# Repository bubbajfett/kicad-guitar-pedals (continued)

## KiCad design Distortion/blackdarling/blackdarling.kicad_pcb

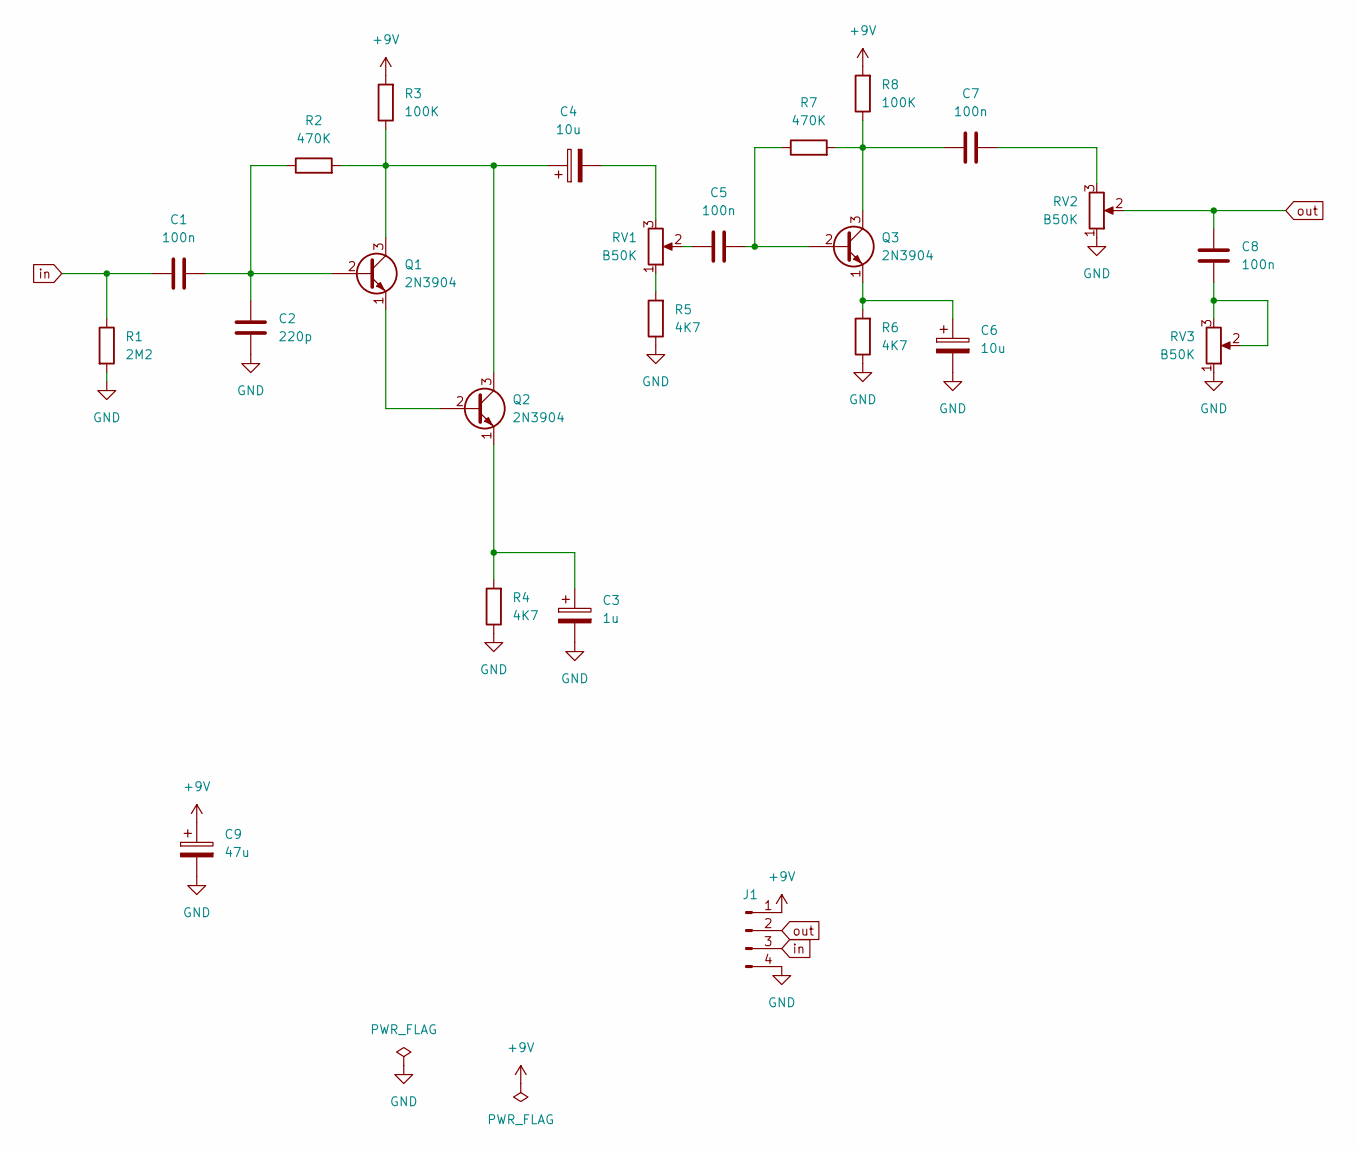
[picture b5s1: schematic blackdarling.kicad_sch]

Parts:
C1, C5, C7, C8: 100n; C_Rect_L7.0mm_W2.5mm_P5.00mm
C2: 220p; C_Disc_D3.8mm_W2.6mm_P2.50mm
C3: 1u; CP_Radial_D5.0mm_P2.00mm
C4, C6: 10u; CP_Radial_D5.0mm_P2.00mm
C9: 47u; CP_Radial_D6.3mm_P2.50mm
J1: Conn_01x04_Pin; PinHeader_1x04_P2.54mm_Vertical
Q1, Q2, Q3: 2N3904; TO-92_Inline
R1: 2M2; R_Axial_DIN0207_L6.3mm_D2.5mm_P10.16mm_Horizontal
R2, R7: 470K; R_Axial_DIN0207_L6.3mm_D2.5mm_P10.16mm_Horizontal
R3, R8: 100K; R_Axial_DIN0207_L6.3mm_D2.5mm_P10.16mm_Horizontal
R4, R5, R6: 4K7; R_Axial_DIN0207_L6.3mm_D2.5mm_P10.16mm_Horizontal
RV1, RV2, RV3: B50K; Pot_Underside

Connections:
+9V: C9.1, J1.1, R3.2, R8.2
GND: C2.1, C3.2, C6.2, C9.2, J1.4, R1.2, R4.1, R5.1, R6.1, RV2.1, RV3.1
unnamed: C4.2, RV1.3
unnamed: C5.1, RV1.2
unnamed: C7.1, RV2.3
unnamed: C8.2, RV3.2, RV3.3
unnamed: C1.2, C2.2, Q1.2 (B), R2.1
unnamed: C4.1, Q1.3 (C), Q2.3 (C), R2.2, R3.1
unnamed: Q1.1 (E), Q2.2 (B)
unnamed: C3.1, Q2.1 (E), R4.2
unnamed: C5.2, Q3.2 (B), R7.1
unnamed: C7.2, Q3.3 (C), R7.2, R8.1
unnamed: C6.1, Q3.1 (E), R6.2
unnamed: R5.2, RV1.1
in: C1.1, J1.3, R1.1
out: C8.1, J1.2, RV2.2

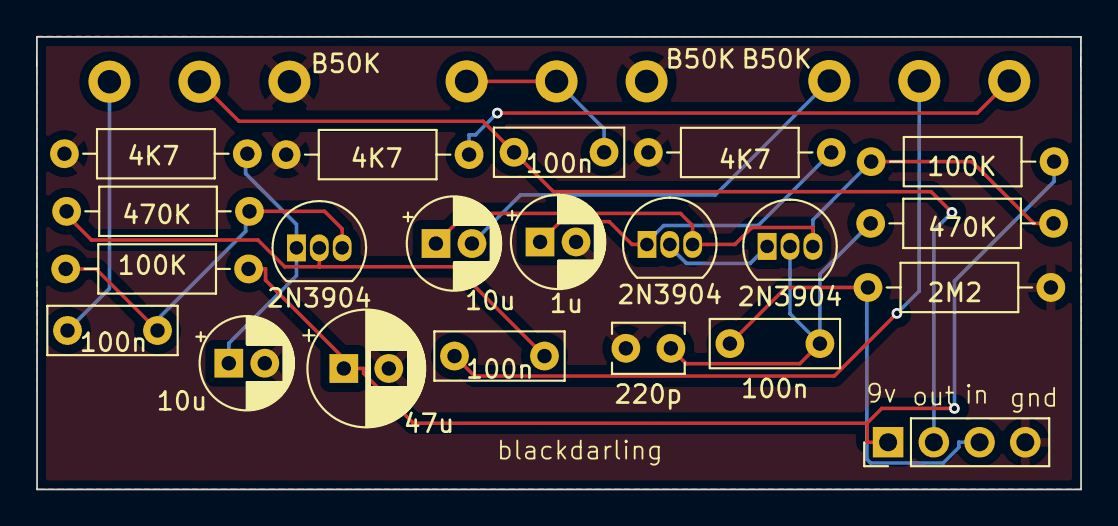
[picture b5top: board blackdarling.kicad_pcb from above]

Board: 2 copper layers, 58.0 x 25.1 mm, 24 parts (0 on the bottom side), 16 nets.

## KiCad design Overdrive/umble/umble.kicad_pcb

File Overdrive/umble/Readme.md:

# Umble

This is from Runoffgrove Umble, and is based on that schematic.

This pedal is verified.  It is very loud.  You must adjust the biases
to around 4.5v on pin3 of each trimmer.

Out of an enclosure it has a lot of noise, which I think is common for
higher-gain pedals.   All 5 controls seem to work the way that they are
intended.

This only has footprints for SMD because I did not think there was enough
room for a through-hole and SMD.    I soldered on the J201 first, and then
used other pads on the empty pcb to test that the soldered J201s were
functional.  All 4 tested out as NJFET with a peak tester.

Sourcing all the pots with a RG097 footprint was a bit of a PITA, but
I do love how tight these are when it is all boxed up.

Not boxed yet, tho.

All trademarks belong to their respective owners.

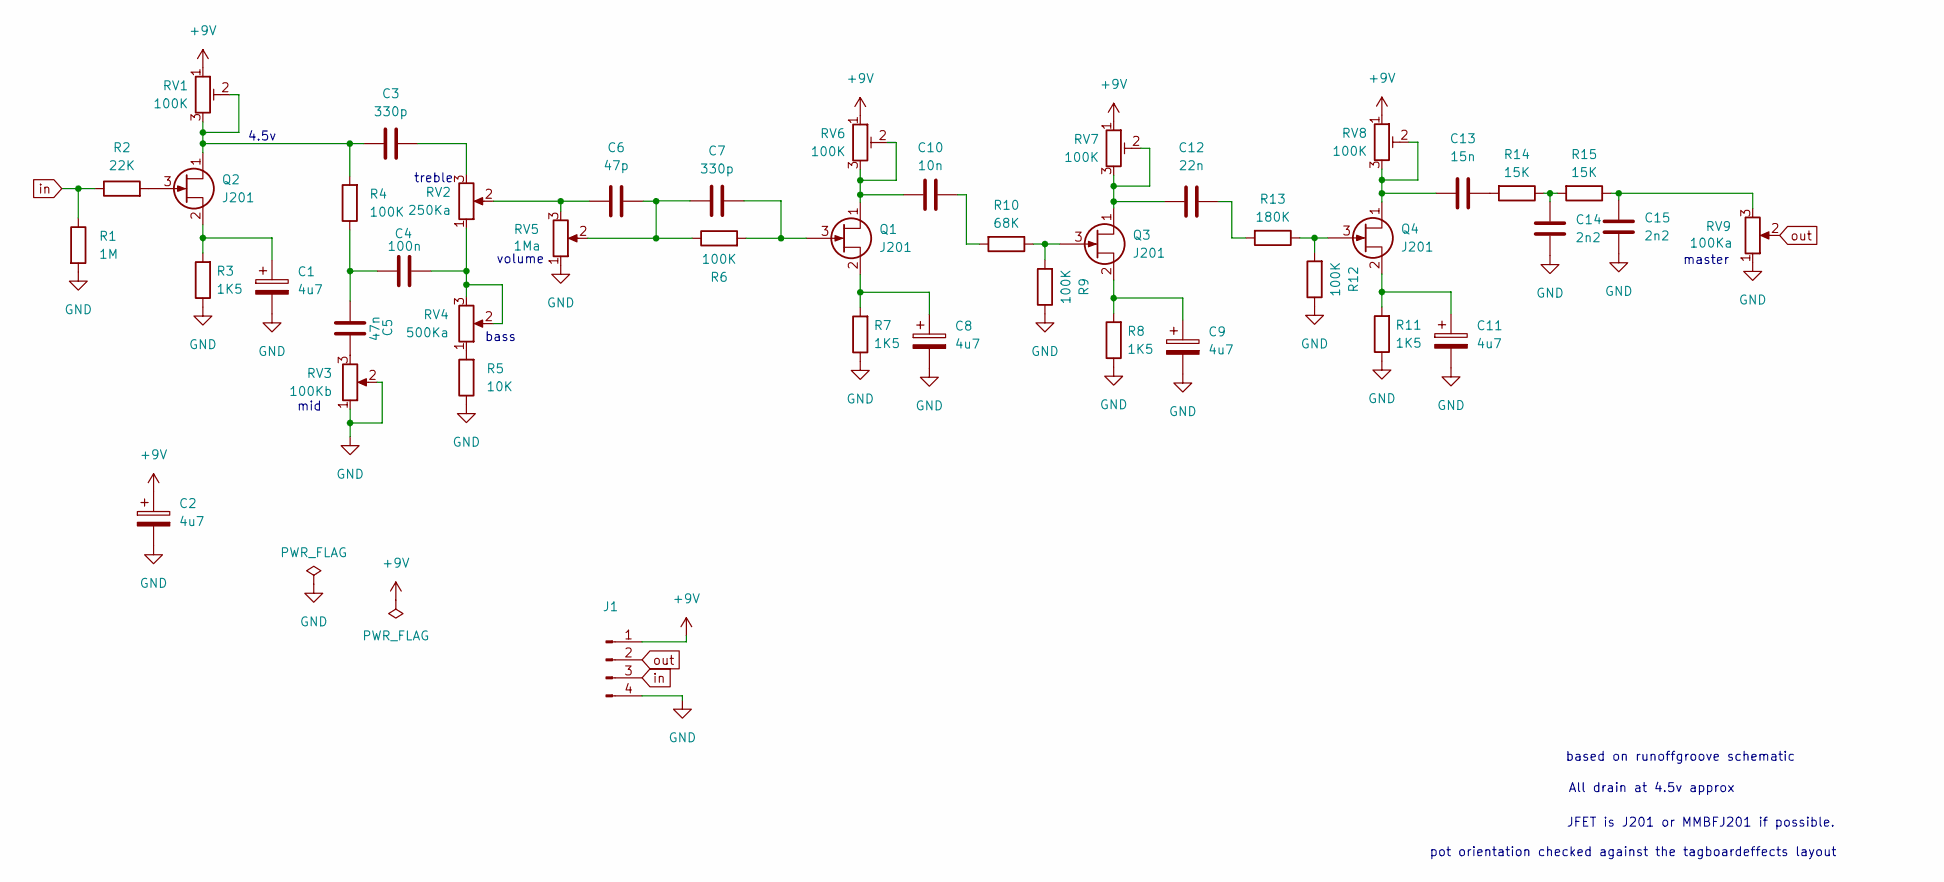
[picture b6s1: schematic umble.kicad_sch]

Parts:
C1, C2, C8, C9, C11: 4u7; CP_Radial_D5.0mm_P2.00mm
C3, C7: 330p; C_Disc_D3.4mm_W2.1mm_P2.50mm
C4: 100n; C_Rect_L7.0mm_W3.5mm_P5.00mm
C5: 47n; C_Rect_L7.0mm_W2.0mm_P5.00mm
C6: 47p; C_Disc_D3.4mm_W2.1mm_P2.50mm
C10: 10n; C_Rect_L7.0mm_W2.0mm_P5.00mm
C12: 22n; C_Rect_L7.0mm_W2.0mm_P5.00mm
C13: 15n; C_Rect_L7.0mm_W2.0mm_P5.00mm
C14, C15: 2n2; C_Rect_L7.0mm_W2.0mm_P5.00mm
J1: Conn_01x04_Pin; PinHeader_1x04_P2.54mm_Vertical
Q1, Q2, Q3, Q4: J201; SOT-23
R1: 1M; R_Axial_DIN0207_L6.3mm_D2.5mm_P7.62mm_Horizontal
R2: 22K; R_Axial_DIN0207_L6.3mm_D2.5mm_P7.62mm_Horizontal
R3, R7, R8, R11: 1K5; R_Axial_DIN0207_L6.3mm_D2.5mm_P7.62mm_Horizontal
R4, R6, R9, R12: 100K; R_Axial_DIN0207_L6.3mm_D2.5mm_P7.62mm_Horizontal
R5: 10K; R_Axial_DIN0207_L6.3mm_D2.5mm_P7.62mm_Horizontal
R10: 68K; R_Axial_DIN0207_L6.3mm_D2.5mm_P7.62mm_Horizontal
R13: 180K; R_Axial_DIN0207_L6.3mm_D2.5mm_P7.62mm_Horizontal
R14, R15: 15K; R_Axial_DIN0207_L6.3mm_D2.5mm_P7.62mm_Horizontal
RV1, RV6, RV7, RV8: 100K; Potentiometer_Runtron_RM-065_Vertical
RV2: 250Ka; Potentiometer_Alps_RK09L_Single_Vertical
RV3: 100Kb; Potentiometer_Alps_RK09L_Single_Vertical
RV4: 500Ka; Potentiometer_Alps_RK09L_Single_Vertical
RV5: 1Ma; Potentiometer_Alps_RK09L_Single_Vertical
RV9: 100Ka; Potentiometer_Alps_RK09L_Single_Vertical

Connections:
+9V: C2.1, J1.1, RV1.1, RV6.1, RV7.1, RV8.1
GND: C1.2, C2.2, C8.2, C9.2, C11.2, C14.1, C15.1, J1.4, R1.2, R3.1, R5.1, R7.1, R8.1, R9.1, R11.1, R12.1, RV3.1, RV3.2, RV5.1, RV9.1
unnamed: C3.2, RV2.3
unnamed: C4.1, C5.1, R4.1
unnamed: C4.2, RV2.1, RV4.2, RV4.3
unnamed: C5.2, RV3.3
unnamed: C6.1, RV2.2, RV5.3
unnamed: C6.2, C7.1, R6.1, RV5.2
unnamed: C10.2, R10.2
unnamed: C12.2, R13.2
unnamed: C13.2, R14.2
unnamed: C14.2, R14.1, R15.2
unnamed: C15.2, R15.1, RV9.3
unnamed: C10.1, Q1.1 (D), RV6.2, RV6.3
unnamed: C7.2, Q1.3 (G), R6.2
unnamed: C8.1, Q1.2 (S), R7.2
unnamed: C3.1, Q2.1 (D), R4.2, RV1.2, RV1.3
unnamed: Q2.3 (G), R2.2
unnamed: C1.1, Q2.2 (S), R3.2
unnamed: C12.1, Q3.1 (D), RV7.2, RV7.3
unnamed: Q3.3 (G), R9.2, R10.1
unnamed: C9.1, Q3.2 (S), R8.2
unnamed: C13.1, Q4.1 (D), RV8.2, RV8.3
unnamed: Q4.3 (G), R12.2, R13.1
unnamed: C11.1, Q4.2 (S), R11.2
unnamed: R5.2, RV4.1
in: J1.3, R1.1, R2.1
out: J1.2, RV9.2

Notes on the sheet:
treble
bass
based on runoffgroove schematic
volume
JFET is J201 or MMBFJ201 if possible.
All drain at 4.5v approx
4.5v
master
pot orientation checked against the tagboardeffects layout
mid

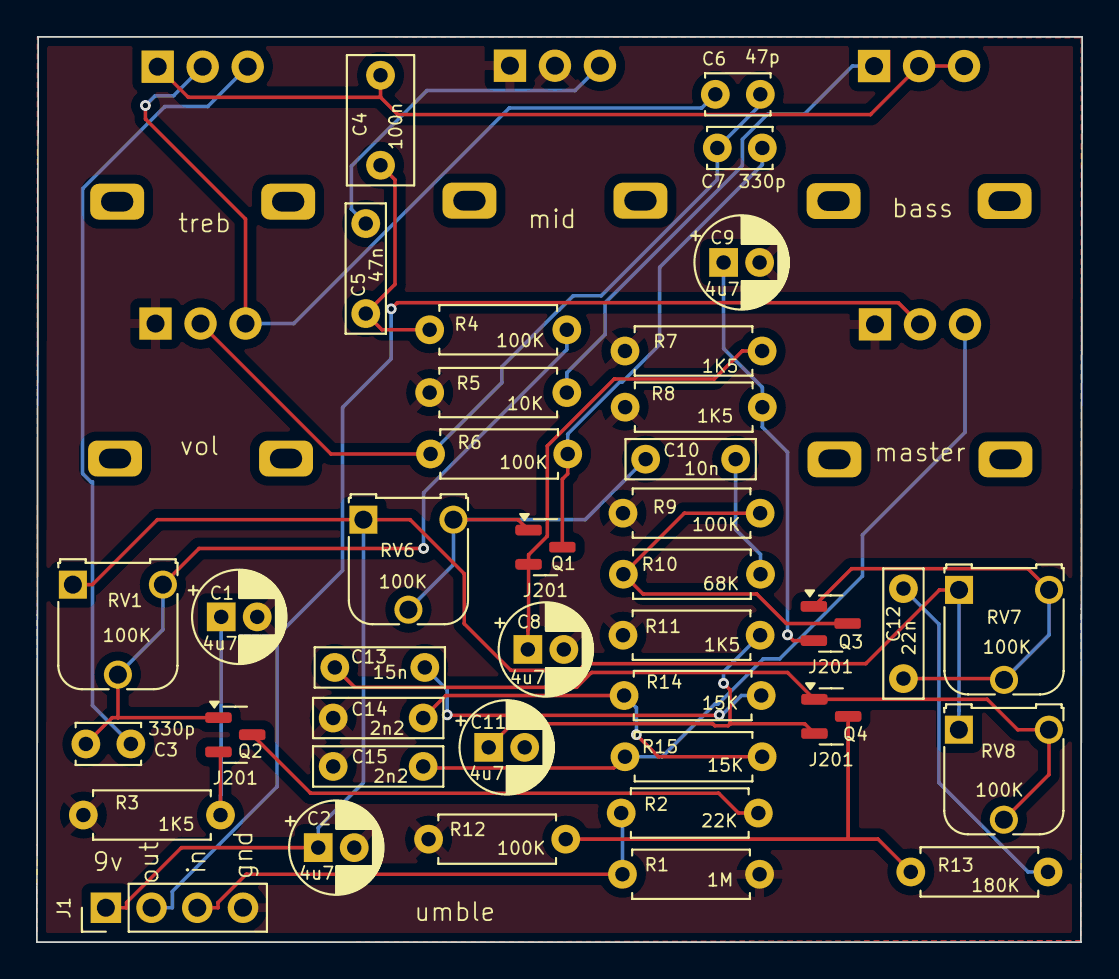
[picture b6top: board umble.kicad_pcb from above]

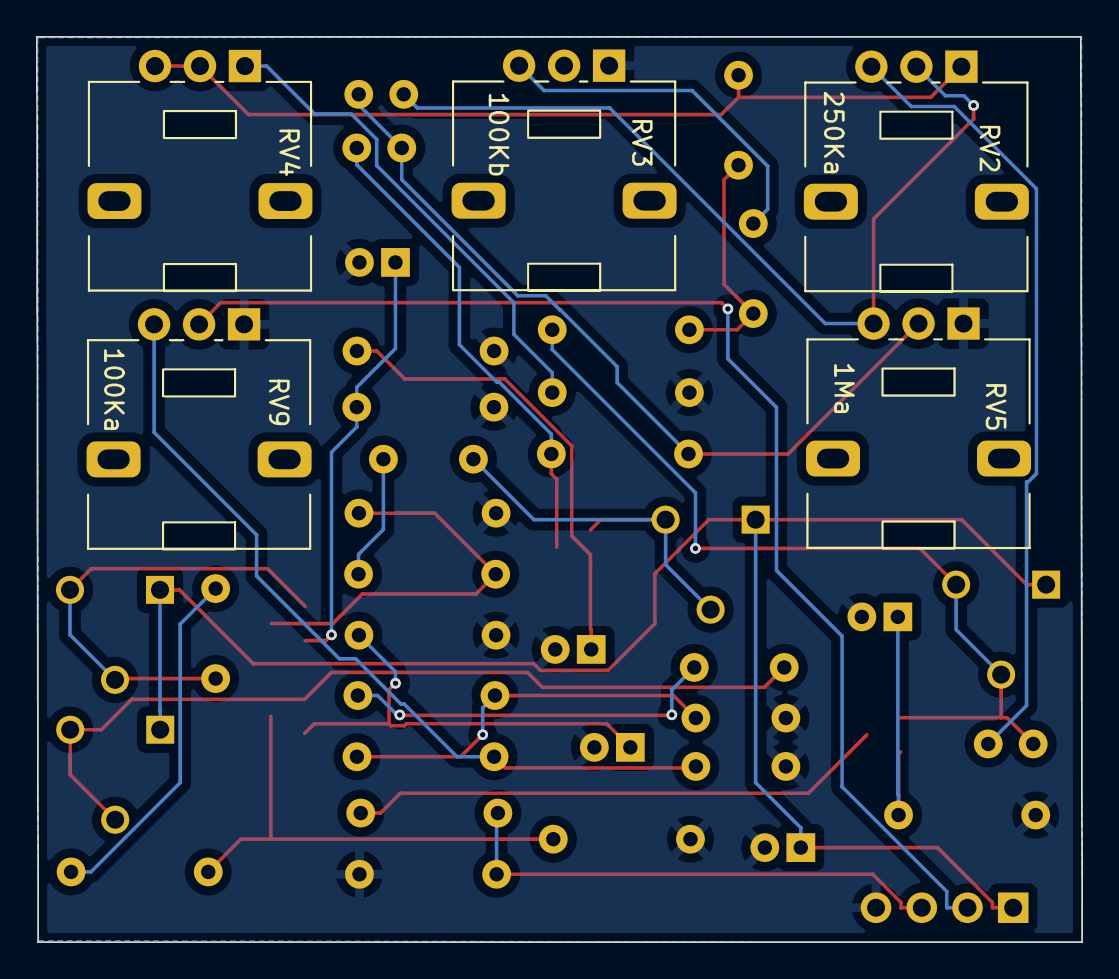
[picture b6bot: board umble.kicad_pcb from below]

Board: 2 copper layers, 58.1 x 50.3 mm, 44 parts (5 on the bottom side), 28 nets.

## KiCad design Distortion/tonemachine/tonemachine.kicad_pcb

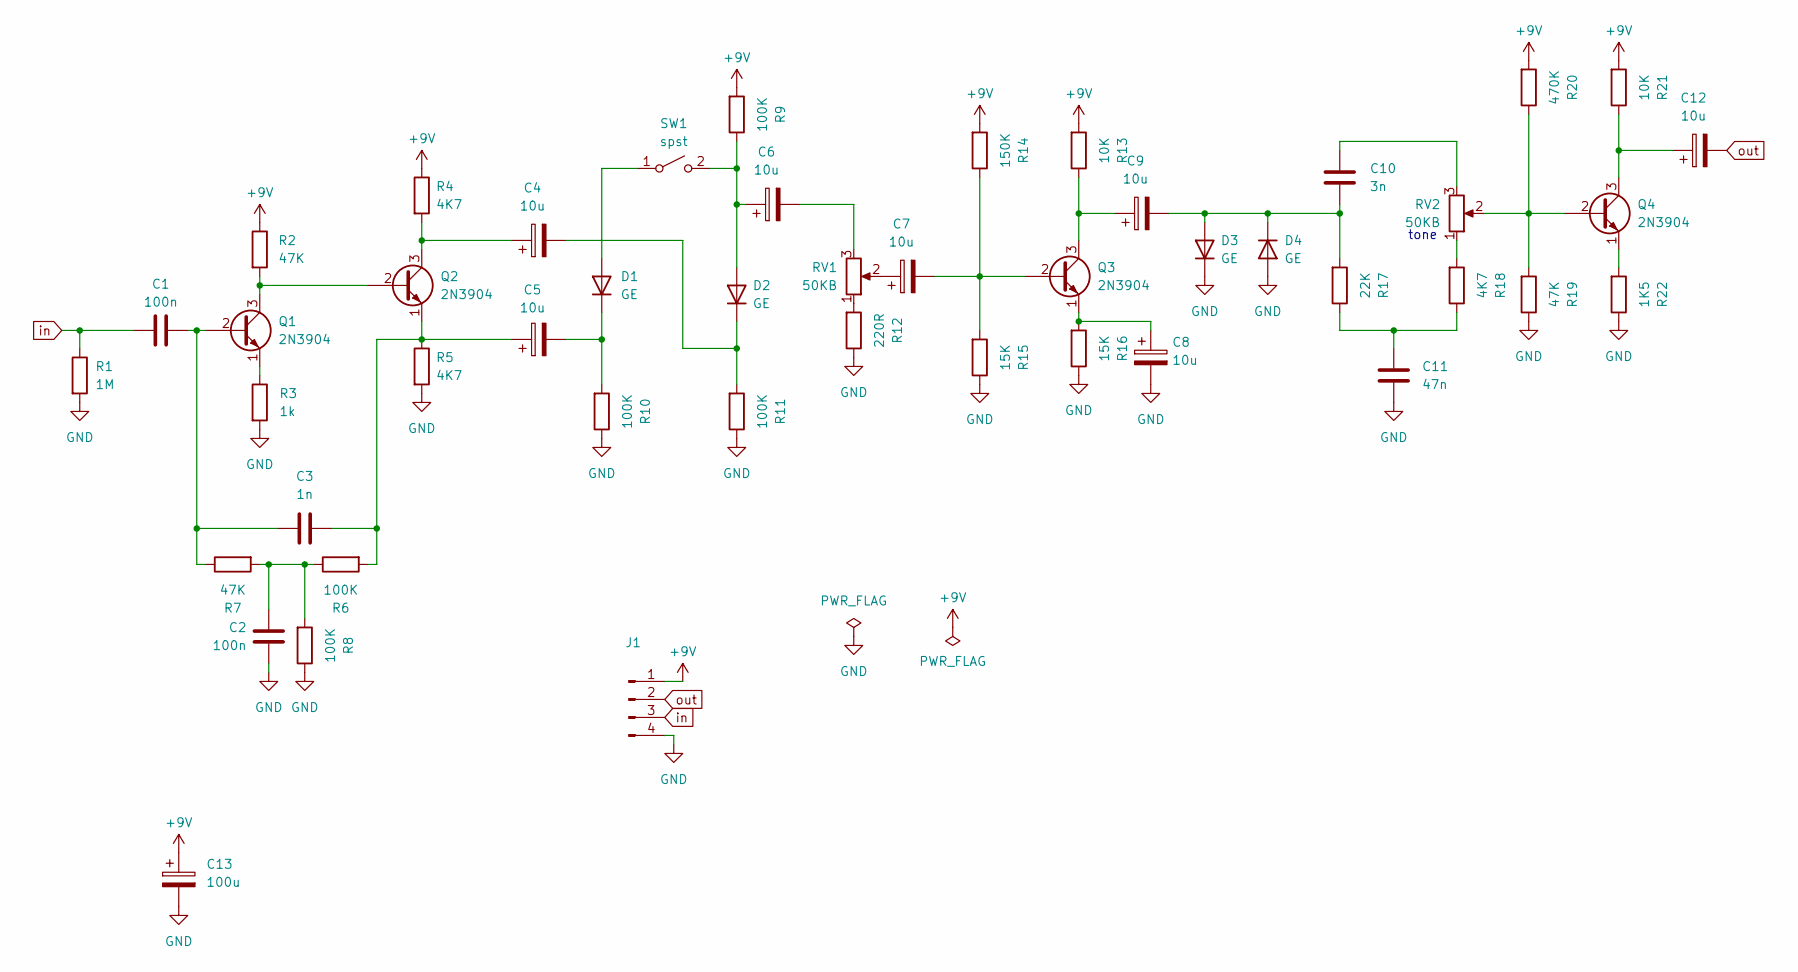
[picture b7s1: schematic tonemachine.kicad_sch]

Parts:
C1, C2: 100n; C_Rect_L7.0mm_W2.5mm_P5.00mm
C3: 1n; C_Rect_L7.0mm_W2.0mm_P5.00mm
C4, C5, C6, C7, C8, C9, C12: 10u; CP_Radial_D5.0mm_P2.00mm
C10: 3n; C_Rect_L7.0mm_W2.0mm_P5.00mm
C11: 47n; C_Rect_L7.0mm_W2.0mm_P5.00mm
C13: 100u; CP_Radial_D6.3mm_P2.50mm
D1, D2, D3, D4: GE; D_DO-34_SOD68_P7.62mm_Horizontal
J1: Conn_01x04_Pin; PinHeader_1x04_P2.54mm_Vertical
Q1, Q2, Q3, Q4: 2N3904; TO-92_Inline
R1: 1M; R_Axial_DIN0207_L6.3mm_D2.5mm_P10.16mm_Horizontal
R2, R7, R19: 47K; R_Axial_DIN0207_L6.3mm_D2.5mm_P10.16mm_Horizontal
R3: 1k; R_Axial_DIN0207_L6.3mm_D2.5mm_P10.16mm_Horizontal
R4, R5, R18: 4K7; R_Axial_DIN0207_L6.3mm_D2.5mm_P10.16mm_Horizontal
R6, R8, R9, R10, R11: 100K; R_Axial_DIN0207_L6.3mm_D2.5mm_P10.16mm_Horizontal
R12: 220R; R_Axial_DIN0207_L6.3mm_D2.5mm_P10.16mm_Horizontal
R13, R21: 10K; R_Axial_DIN0207_L6.3mm_D2.5mm_P10.16mm_Horizontal
R14: 150K; R_Axial_DIN0207_L6.3mm_D2.5mm_P10.16mm_Horizontal
R15, R16: 15K; R_Axial_DIN0207_L6.3mm_D2.5mm_P10.16mm_Horizontal
R17: 22K; R_Axial_DIN0207_L6.3mm_D2.5mm_P10.16mm_Horizontal
R20: 470K; R_Axial_DIN0207_L6.3mm_D2.5mm_P10.16mm_Horizontal
R22: 1K5; R_Axial_DIN0207_L6.3mm_D2.5mm_P10.16mm_Horizontal
RV1, RV2: 50KB; Pot_Underside
SW1: spst; SWITCH-M1-SPDT

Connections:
+9V: C13.1, J1.1, R2.1, R4.1, R9.2, R13.2, R14.2, R20.2, R21.2
GND: C2.1, C8.2, C11.2, C13.2, D3.1 (K), D4.2 (A), J1.4, R1.2, R3.2, R5.2, R8.1, R10.1, R11.1, R12.1, R15.1, R16.1, R19.1, R22.1
unnamed: C2.2, R6.1, R7.2, R8.2
unnamed: C6.2, RV1.3
unnamed: C7.1, RV1.2
unnamed: C10.1, RV2.3
unnamed: C11.1, R17.1, R18.1
unnamed: D1.2 (A), SW1.1 (A)
unnamed: C5.2, D1.1 (K), R10.2
unnamed: C6.1, D2.2 (A), R9.1, SW1.2 (B)
unnamed: C4.2, D2.1 (K), R11.2
unnamed: C9.2, C10.2, D3.2 (A), D4.1 (K), R17.2
unnamed: C1.2, C3.2, Q1.2 (B), R7.1
unnamed: Q1.3 (C), Q2.2 (B), R2.2
unnamed: Q1.1 (E), R3.1
unnamed: C4.1, Q2.3 (C), R4.2
unnamed: C3.1, C5.1, Q2.1 (E), R5.1, R6.2
unnamed: C7.2, Q3.2 (B), R14.1, R15.2
unnamed: C9.1, Q3.3 (C), R13.1
unnamed: C8.1, Q3.1 (E), R16.2
unnamed: Q4.2 (B), R19.2, R20.1, RV2.2
unnamed: C12.1, Q4.3 (C), R21.1
unnamed: Q4.1 (E), R22.2
unnamed: R12.2, RV1.1
unnamed: R18.2, RV2.1
in: C1.1, J1.3, R1.1
out: C12.2, J1.2

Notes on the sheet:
tone

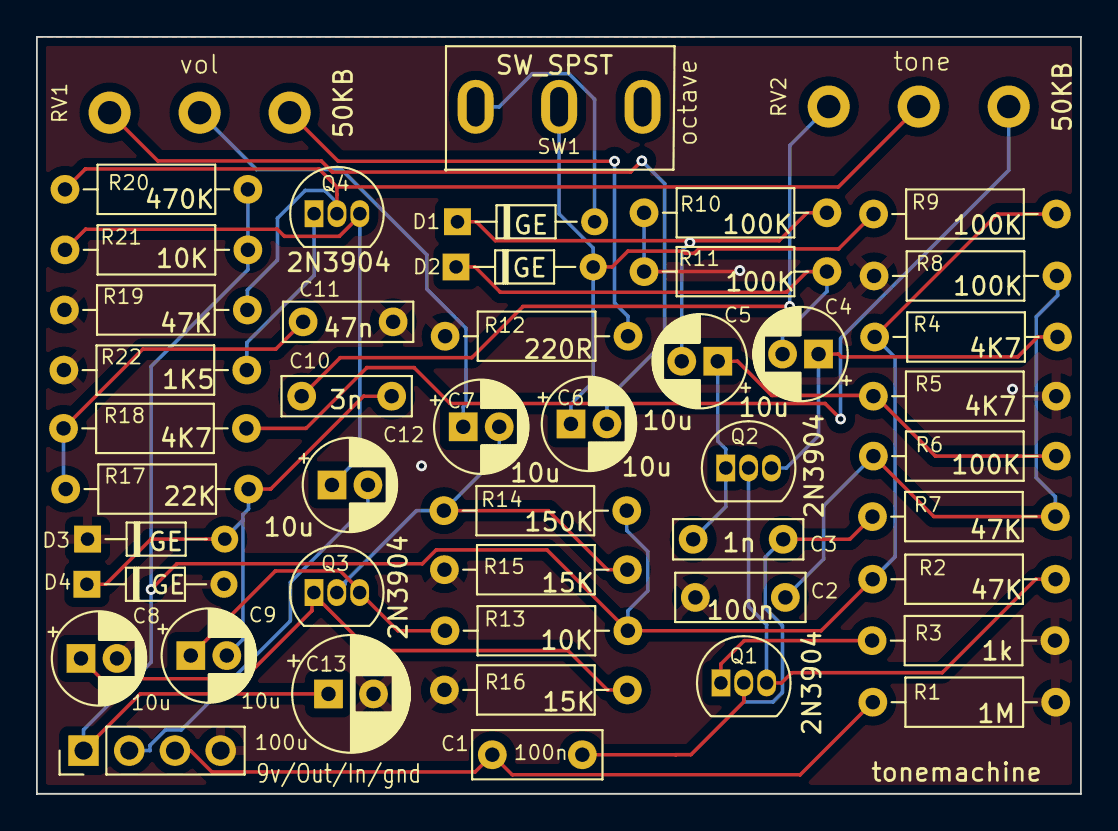
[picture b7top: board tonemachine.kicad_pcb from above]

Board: 2 copper layers, 58.0 x 42.0 mm, 47 parts (0 on the bottom side), 27 nets.

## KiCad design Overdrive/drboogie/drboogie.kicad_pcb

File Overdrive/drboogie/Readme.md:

# Dr Boogieclone

This is based on the Mesa Boogie Dual Rectifier Solo Amplifier.   It is a
high-gain overdrive pedal.   I think it is designed by ElectraTabs over
on the  DIYStompboxes forum. 

This is the 2nd version of the board.
The original version worked too, but the
pots were wrong footprint, so they increased anti-clockwise.   The build
was done with MMBFJ201 JFETs.  This has dual footprints for the JFETs.
These were soldered in first, and tested using pins in the
through-hole part of the footprint.    The main deviation on my
build is an A25K footprint in the smaller RK09 potentiometers is apparently
unobtainable, so a B20K was used instead.

This is sized for a 125B.   Hope it fits.

I had thought, on first testing, that this sounded splatty and hugely over 
distorted, but I had guitar on max volume.    Turning it down a bit made it
sound so much better.

Apparently the trimpots need to be adjusted for 4.5 on the drain of
the corresponding JFET.   I haven't done that yet; all the trims are at 50%.

Very nice high-gain overdrive.    I now have 3 builds prior in a row on the
box-of-shame, so it was nice to hear this light up!!!!

All trademarks belong to their respective trademark owners.

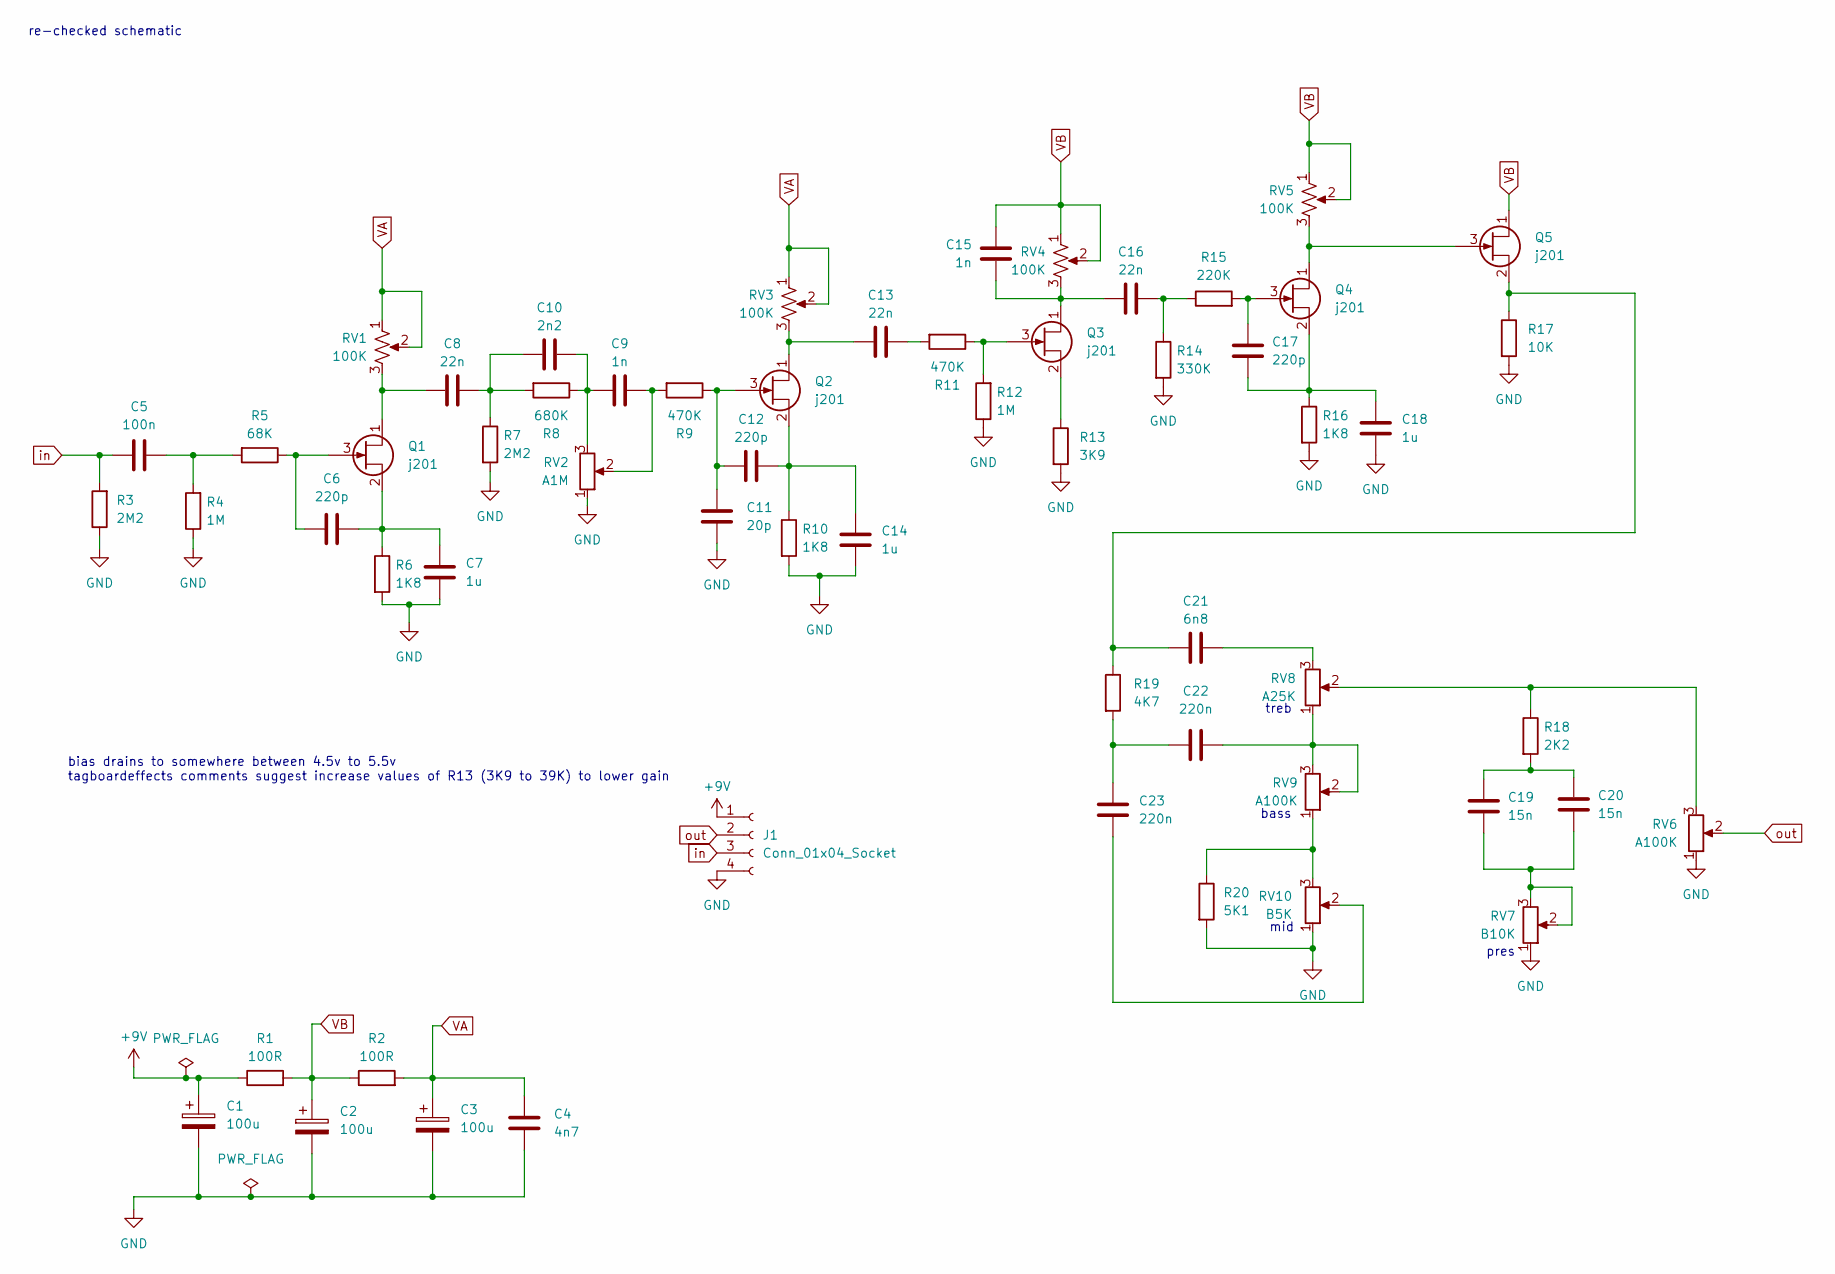
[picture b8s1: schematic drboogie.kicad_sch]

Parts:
C1, C2, C3: 100u; CP_Radial_D6.3mm_P2.50mm
C4: 4n7; C_Rect_L7.0mm_W3.5mm_P5.00mm
C5: 100n; C_Rect_L7.0mm_W3.5mm_P5.00mm
C6: 220p; C_Rect_L7.0mm_W3.5mm_P5.00mm
C7, C14, C18: 1u; C_Rect_L7.0mm_W4.5mm_P5.00mm
C8, C13, C16: 22n; C_Rect_L7.0mm_W3.5mm_P5.00mm
C9: 1n; C_Rect_L7.0mm_W3.5mm_P5.00mm
C10: 2n2; C_Rect_L7.0mm_W3.5mm_P5.00mm
C11: 20p; C_Rect_L7.0mm_W2.0mm_P5.00mm
C12, C17: 220p; C_Rect_L7.0mm_W2.0mm_P5.00mm
C15: 1n; C_Rect_L7.0mm_W4.5mm_P5.00mm
C19, C20: 15n; C_Rect_L7.0mm_W3.5mm_P5.00mm
C21: 6n8; C_Rect_L7.0mm_W3.5mm_P5.00mm
C22, C23: 220n; C_Rect_L7.0mm_W3.5mm_P5.00mm
J1: Conn_01x04_Socket; PinHeader_1x04_P2.54mm_Vertical
Q1, Q2, Q3, Q4, Q5: j201; TO92-SMD
R1, R2: 100R; R_Axial_DIN0207_L6.3mm_D2.5mm_P10.16mm_Horizontal
R3, R7: 2M2; R_Axial_DIN0207_L6.3mm_D2.5mm_P10.16mm_Horizontal
R4, R12: 1M; R_Axial_DIN0207_L6.3mm_D2.5mm_P10.16mm_Horizontal
R5: 68K; R_Axial_DIN0207_L6.3mm_D2.5mm_P10.16mm_Horizontal
R6, R10, R16: 1K8; R_Axial_DIN0207_L6.3mm_D2.5mm_P10.16mm_Horizontal
R8: 680K; R_Axial_DIN0207_L6.3mm_D2.5mm_P10.16mm_Horizontal
R9, R11: 470K; R_Axial_DIN0207_L6.3mm_D2.5mm_P10.16mm_Horizontal
R13: 3K9; R_Axial_DIN0207_L6.3mm_D2.5mm_P10.16mm_Horizontal
R14: 330K; R_Axial_DIN0207_L6.3mm_D2.5mm_P10.16mm_Horizontal
R15: 220K; R_Axial_DIN0207_L6.3mm_D2.5mm_P10.16mm_Horizontal
R17: 10K; R_Axial_DIN0207_L6.3mm_D2.5mm_P10.16mm_Horizontal
R18: 2K2; R_Axial_DIN0207_L6.3mm_D2.5mm_P10.16mm_Horizontal
R19: 4K7; R_Axial_DIN0207_L6.3mm_D2.5mm_P10.16mm_Horizontal
R20: 5K1; R_Axial_DIN0207_L6.3mm_D2.5mm_P10.16mm_Horizontal
RV1, RV3, RV4, RV5: 100K; Potentiometer_Runtron_RM-065_Vertical
RV2: A1M; Potentiometer_Alps_RK09L_Single_Vertical
RV6, RV9: A100K; Potentiometer_Alps_RK09L_Single_Vertical
RV7: B10K; Potentiometer_Alps_RK09L_Single_Vertical
RV8: A25K; Potentiometer_Alps_RK09L_Single_Vertical
RV10: B5K; Potentiometer_Alps_RK09L_Single_Vertical

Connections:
+9V: C1.1, J1.1, R1.1
GND: C1.2, C2.2, C3.2, C4.2, C7.1, C11.2, C14.1, C18.1, J1.4, R3.1, R4.1, R6.2, R7.2, R10.2, R12.1, R13.2, R14.2, R16.2, R17.2, R20.2, RV2.1, RV6.1, RV7.1, RV10.1
unnamed: C5.2, R4.2, R5.2
unnamed: C9.1, R9.2, RV2.2
unnamed: C9.2, C10.1, R8.1, RV2.3
unnamed: C8.1, C10.2, R7.1, R8.2
unnamed: C13.1, R11.2
unnamed: C16.1, R14.1, R15.1
unnamed: C19.1, C20.1, RV7.2, RV7.3
unnamed: C19.2, C20.2, R18.2
unnamed: C21.1, RV8.3
unnamed: C22.1, RV8.1, RV9.2, RV9.3
unnamed: C22.2, C23.1, R19.2
unnamed: C23.2, RV10.2
unnamed: C8.2, Q1.1 (D), RV1.3
unnamed: C6.1, Q1.3 (G), R5.1
unnamed: C6.2, C7.2, Q1.2 (S), R6.1
unnamed: C13.2, Q2.1 (D), RV3.3
unnamed: C11.1, C12.1, Q2.3 (G), R9.1
unnamed: C12.2, C14.2, Q2.2 (S), R10.1
unnamed: C15.2, C16.2, Q3.1 (D), RV4.3
unnamed: Q3.3 (G), R11.1, R12.2
unnamed: Q3.2 (S), R13.1
unnamed: Q4.1 (D), Q5.3 (G), RV5.3
unnamed: C17.2, Q4.3 (G), R15.2
unnamed: C17.1, C18.2, Q4.2 (S), R16.1
unnamed: C21.2, Q5.2 (S), R17.1, R19.1
unnamed: R18.1, RV6.3, RV8.2
unnamed: R20.1, RV9.1, RV10.3
VA: C3.1, C4.1, R2.2, RV1.1, RV1.2, RV3.1, RV3.2
VB: C2.1, C15.1, Q5.1 (D), R1.2, R2.1, RV4.1, RV4.2, RV5.1, RV5.2
in: C5.1, J1.3, R3.2
out: J1.2, RV6.2

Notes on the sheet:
pres
mid
re-checked schematic
treb
bias drains to somewhere between 4.5v to 5.5v tagboardeffects comments suggest increase values of R13 (3K9 to 39K) to lower gain
bass

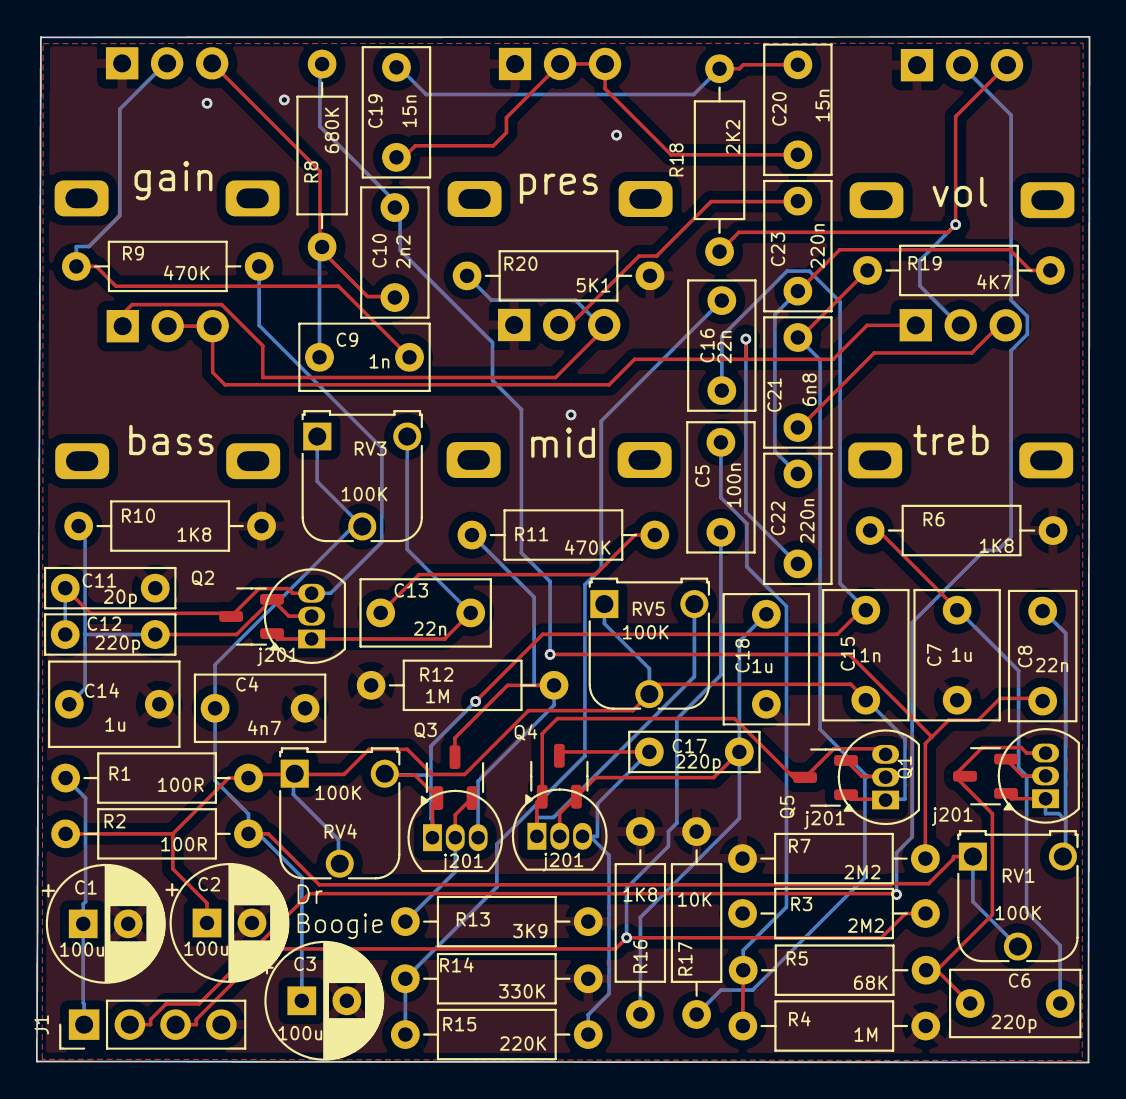
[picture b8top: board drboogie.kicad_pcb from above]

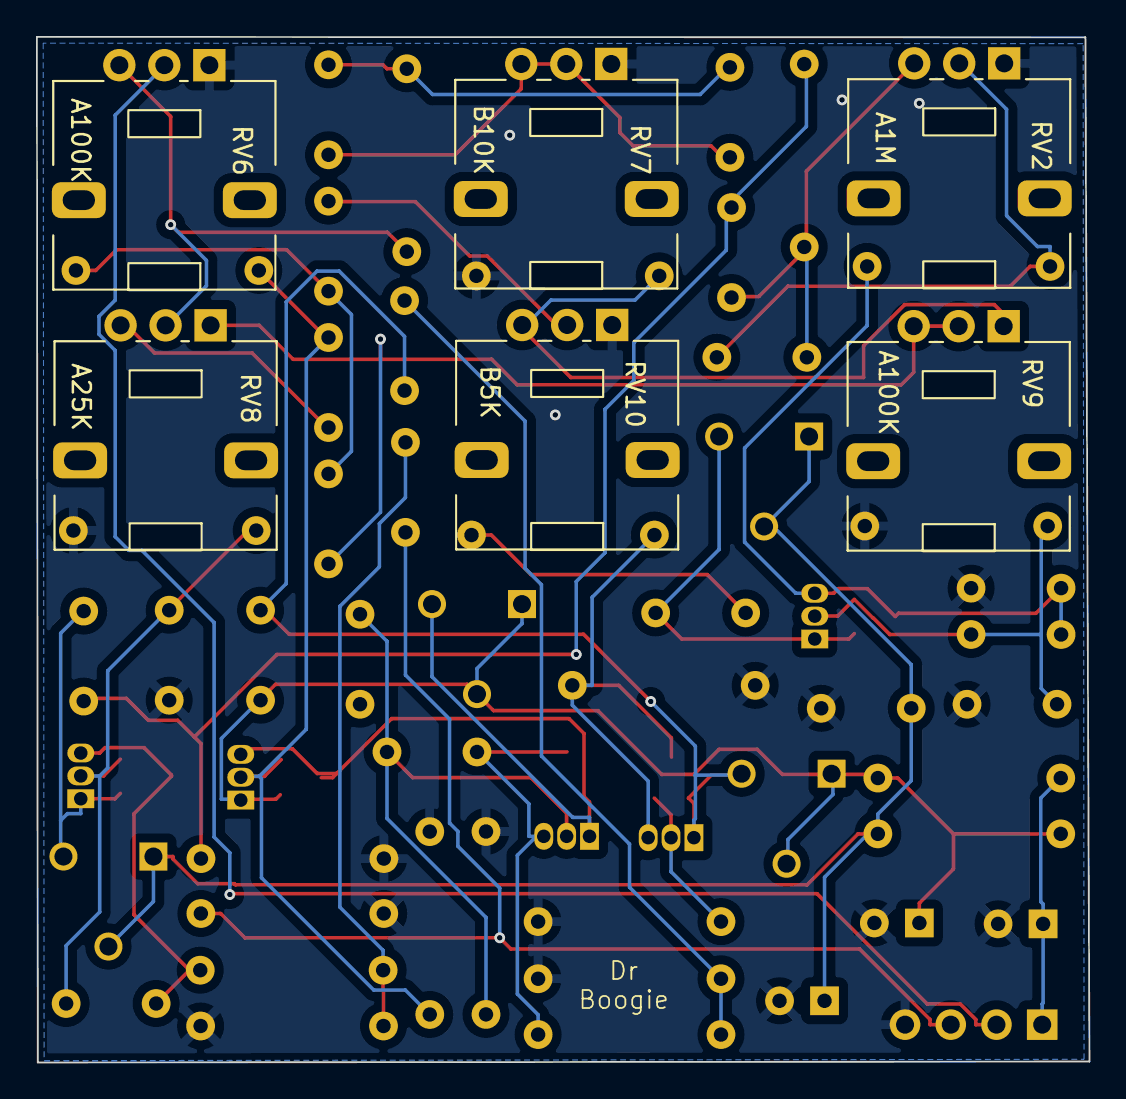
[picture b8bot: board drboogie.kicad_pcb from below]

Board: 2 copper layers, 58.5 x 57.0 mm, 59 parts (6 on the bottom side), 33 nets.

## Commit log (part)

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2026-02-08 Moving repos into a single repo
2026-02-08 added two additional pedals -- whitefuzz and harmonicpercolator
2026-02-22 Added timmy drive
2026-02-22 Added timmy
2026-02-27 added tweed57 overdrive
    updated layout of the chargepump pcb
2026-03-01 added the badmonkey pedal
2026-03-04 added fatdrive
2026-03-09 re-generated the Fatdrive and badmonkey boards, as they were just a hair too large for the enclosures I am using.
    x
2026-03-16 Added Overdrive-07-ecstacy
2026-03-16 Added Readme.md
2026-03-16 added acapulco gold
2026-03-16 removed zip file
2026-04-02 reorg
2026-04-02 missing files
2026-04-02 cleanup
2026-04-15 mutron prl
2026-04-25 fix to badmonkey -- pedal works but the schematic this was based on does not seem right. There's a voltage offset on the input when engaged, and this messes with it in the pedal chain.
2026-05-03 added 6 band eq, and fuzzface distortion
2026-05-03 added deep_blue_delay
2026-05-16 added repo listing
2026-05-23 updated readme, comments on fatdrive schematic
2026-05-25 added triple wreck
2026-05-26 added triple_wreck
2026-05-27 added overdrive/ocd
2026-06-08 added engineers thumb, ramshead-bmp
2026-06-09 added top-jacks and stomp-3pdt
2026-06-25 added ejfuzzface
2026-06-27 replaced whiefuzz, and modified ejfuzzface
2026-06-28 top jacks gerbers.
